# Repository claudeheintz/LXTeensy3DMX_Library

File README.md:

# LXTeensy3DMX
DMX Driver for Teensy 3.x using Teensyduino

   LXTeensyDMX is a driver for sending or receiving DMX using a Teensy 3.x's UART0 RX pin 0, TX pin 1
   
   LXTeensyDMX output mode continuously sends DMX once its interrupts have been enabled using startOutput().
   Use setSlot() to set the level value for a particular DMX dimmer/address/channel.
   
   LXTeensyDMX input mode continuously receives DMX once its interrupts have been enabled using startInput()
   Use getSlot() to read the level value for a particular DMX dimmer/address/channel.
   
   LXTeensyDMX rdm mode allows both sending and receiving. RDM mode can continuously send DMX, the same as when using output mode.  But, RDM mode can also pause regular DMX (zero start code) to send an RDM message and wait for a reply.  RDM mode can also be used to listen for both regular and RDM packets, responding to the RDM messages by sending replies.
   
   LXTeensyDMX is used with a single instance called Teensy3DMX	

   Additional instances using UART1 and UART2 are available by using Teensy3DMX1 and Teensy3DMX2.
   
   LXTeensyDMX has been tested with Teensy 3.2 and 3.6

   Support for Teensy4 is a separate project on GiHub:
   https://github.com/claudeheintz/LXTeensy4DMX_Library

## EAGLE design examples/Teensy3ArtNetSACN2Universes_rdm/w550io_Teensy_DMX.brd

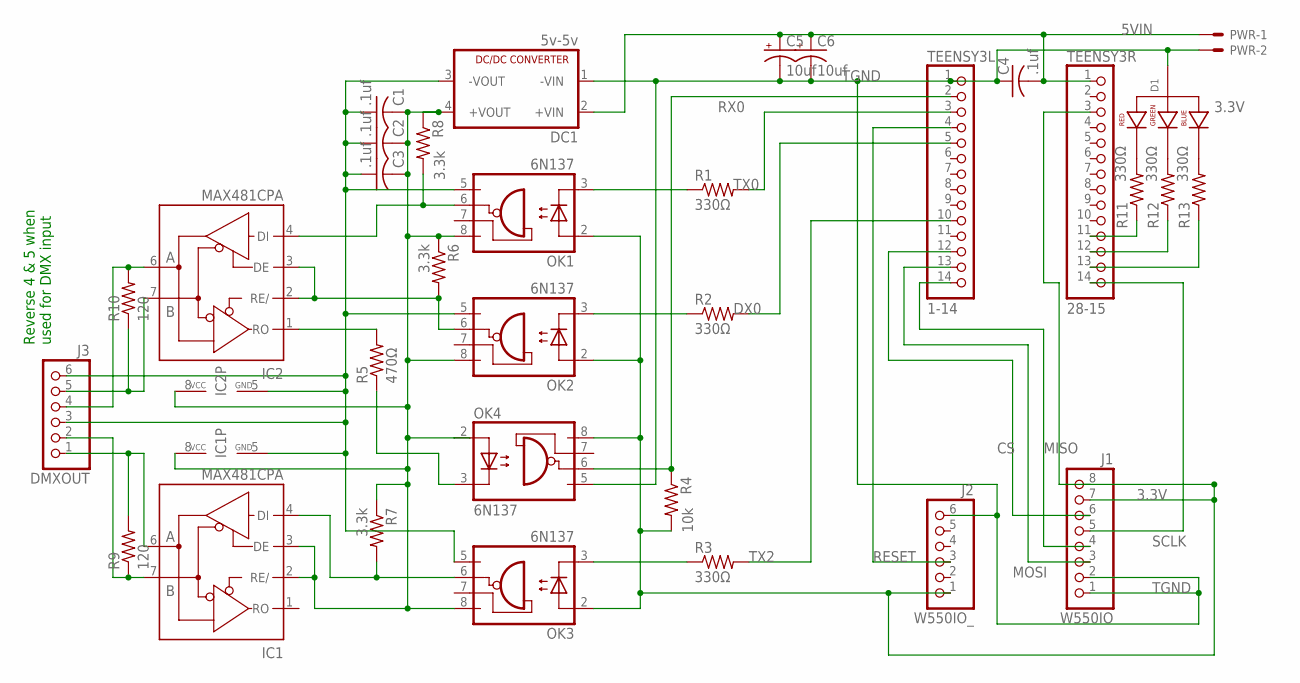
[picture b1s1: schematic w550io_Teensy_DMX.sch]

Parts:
C1, C2, C3, C4: .1uf; C050-024X044
C5, C6: 10uf; B45181B
D1: LED-RGB-CA-THRUCLEAR; LED-RGB-THRU
DC1: 5v-5v; NME
DMXOUT: J3; 1X06-BIG
IC1, IC2: MAX481CPA; DIL08
OK1, OK2, OK3, OK4: 6N137; DIL08
PWR: 22-23-2021
R1, R2, R3, R11, R12, R13: 330Ω; 0204/5
R4: 10k; 0204/5
R5: 470Ω; 0204/5
R6, R7, R8: 3.3k; 0204/5
R9, R10: 120; 0204/5
TEENSY3L: 1-14; 1X14
TEENSY3R: 28-15; 1X14
W550IO: J1; 1X08-BIG
W550IO_: J2; 1X06-BIG

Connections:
3.3V: OK1.2 (A), OK2.2 (A), OK3.2 (A), OK4.8 (VCC), R4.2, TEENSY3R.3, W550IO.7, W550IO.8, W550IO_.1
5VIN: C4.2, C5.+, C6.+, DC1.2 (+VIN), PWR.1, TEENSY3R.1
CS: TEENSY3L.12, W550IO.6
DX0: R2.2, TEENSY3L.5
GND: C1.1, C2.1, C3.1, DC1.3 (-VOUT), DMXOUT.3, DMXOUT.6, IC1.5 (GND), IC2.5 (GND), OK1.5 (GND), OK2.5 (GND), OK3.5 (GND)
MISO: TEENSY3L.14, W550IO.4
MOSI: TEENSY3L.13, W550IO.3
unnamed: OK4.3 (C), R5.1
unnamed: DMXOUT.4, IC2.6 (A), R10.2
unnamed: DMXOUT.1, IC1.6 (A), R9.2
unnamed: DMXOUT.2, IC1.7 (B), R9.1
unnamed: OK1.3 (C), R1.1
unnamed: OK2.3 (C), R2.1
unnamed: OK3.3 (C), R3.1
unnamed: IC1.4 (DI), OK3.6 (VO), R7.2
unnamed: DMXOUT.5, IC2.7 (B), R10.1
unnamed: D1.1 (RED_CATHODE), R11.2
unnamed: D1.3 (GREEN_CATHODE), R12.2
unnamed: IC2.1 (RO), R5.2
unnamed: IC2.2 (RE/), IC2.3 (DE), OK2.6 (VO), R6.2
unnamed: IC2.4 (DI), OK1.6 (VO), R8.2
unnamed: D1.4 (BLUE_CATHODE), R13.2
unnamed: R13.1, TEENSY3R.13
unnamed: R12.1, TEENSY3R.12
unnamed: R11.1, TEENSY3R.11
RESET: TEENSY3L.4, W550IO_.3
RX0: OK4.6 (VO), R4.1, TEENSY3L.2
SCLK: TEENSY3R.14, W550IO.5
TGND: C4.1, C5.-, C6.-, D1.2 (ANODE), DC1.1 (-VIN), OK4.5 (GND), PWR.2, TEENSY3L.1, W550IO.1, W550IO.2, W550IO_.6
TX0: R1.2, TEENSY3L.3
TX2: R3.2, TEENSY3L.10
VCC: C1.2, C2.2, C3.2, DC1.4 (+VOUT), IC1.2 (RE/), IC1.3 (DE), IC1.8 (VCC), IC2.8 (VCC), OK1.8 (VCC), OK2.8 (VCC), OK3.8 (VCC), OK4.2 (A), R6.1, R7.1, R8.1

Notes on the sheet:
Reverse 4 & 5 when used for DMX input

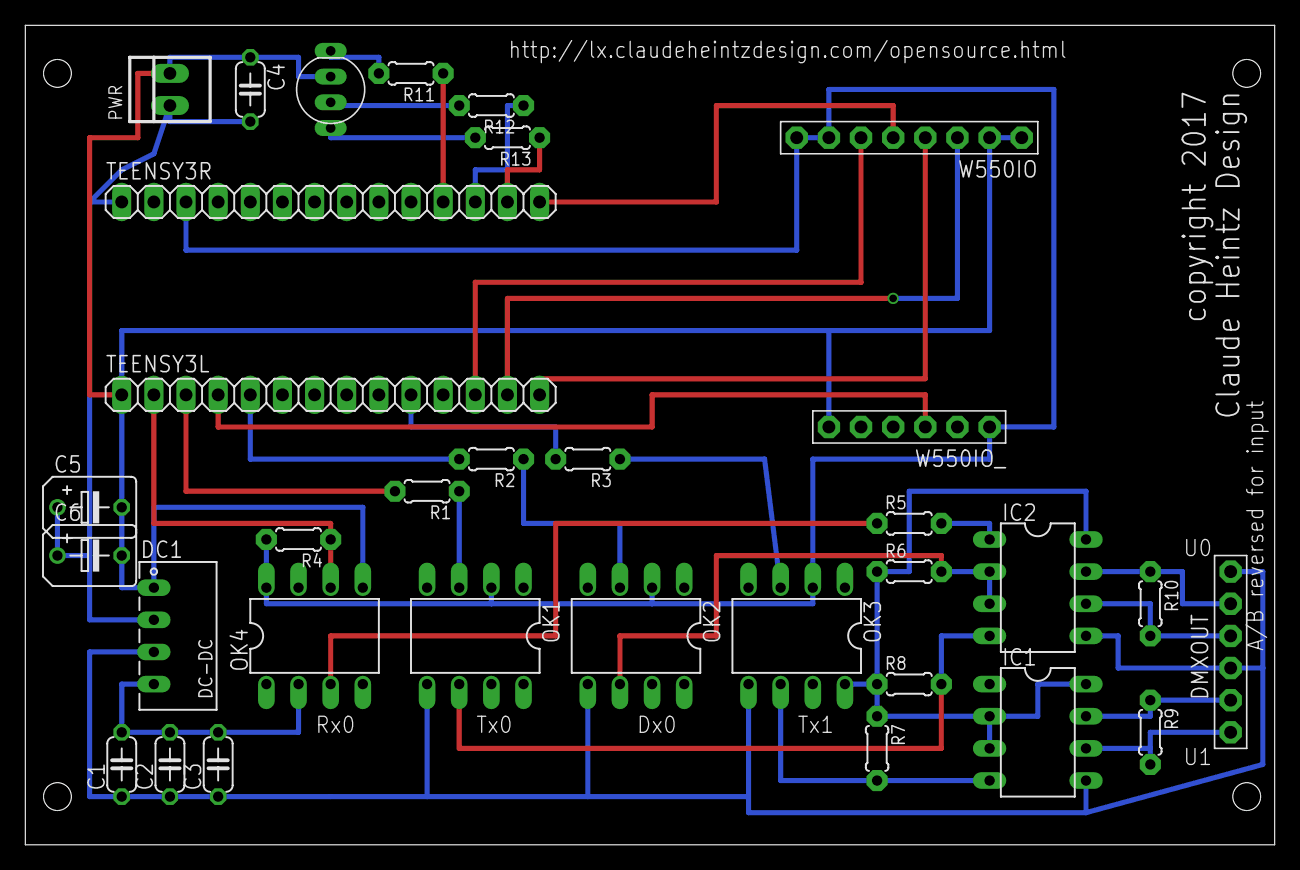
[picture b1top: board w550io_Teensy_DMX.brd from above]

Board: 2 copper layers, 98.7 x 64.8 mm, 33 parts (0 on the bottom side), 32 nets.

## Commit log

2016-01-18 restored proper first commit
2016-01-18 created gitignore
2016-05-16 Added FTDI Example
    Example uses external FTDI to USB adapter which allows DMX USB Pro
    emulation with software that only supports FTDI d2xx driver.
2016-06-05 support for additional 2 universes
    Adds support for an additional 2 universes using UART1 and UART2
2016-06-05 Added 2 Universe Example
2017-01-03 Add volatile keyword
2017-01-03 Add Art-Net/sACN Example
    Includes Eagle Files for 2 Universe Art-Net/sACN interface
2017-01-06 Change Board to output only
    Bi-directional design power is unstable. Previous design is functional
    by not populating input and direction optocouplers.
2017-01-07 Changed 10k Resistors to 1k
2017-01-09 Changed resistors to 3.3k
2017-01-09 Fix DMX input / example schematic
2017-09-19 add rdm support
2017-09-19 update examples for rdm
2017-09-22 update example for renew/rebind DHCP lease
2017-09-26 fix sending extra byte with RDM
2017-10-04 Update RDM code and example
2017-10-04 update rdm code
2017-10-26 update example
2018-02-23 refactor rdm/UID.h
2018-02-23 rename UID::copyFromUID
    Name change makes it more apparent what the static method does
2018-03-04 update read me
2020-02-03 abstracted UART Hardware
2020-02-03 correct baud divisor for UART2
2020-02-04 remove warning
2020-02-06 update for 3.6 stop bits
2020-02-06 remove experimental break detect
2020-02-07 BAUD2DIV macros in hardware_uart_set_baud
2020-02-07 Fix input baud
2020-02-09 update RDM example

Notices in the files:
examples/Teensy3ArtNetSACN2Universes_rdm/w550io_Teensy_DMX.brd:
copyright 2017
parts and their libraries:
SparkFun-LED: Licensing: Creative Commons ShareAlike 4.0 International - https://creativecommons.org/licenses/by-sa/4.0
